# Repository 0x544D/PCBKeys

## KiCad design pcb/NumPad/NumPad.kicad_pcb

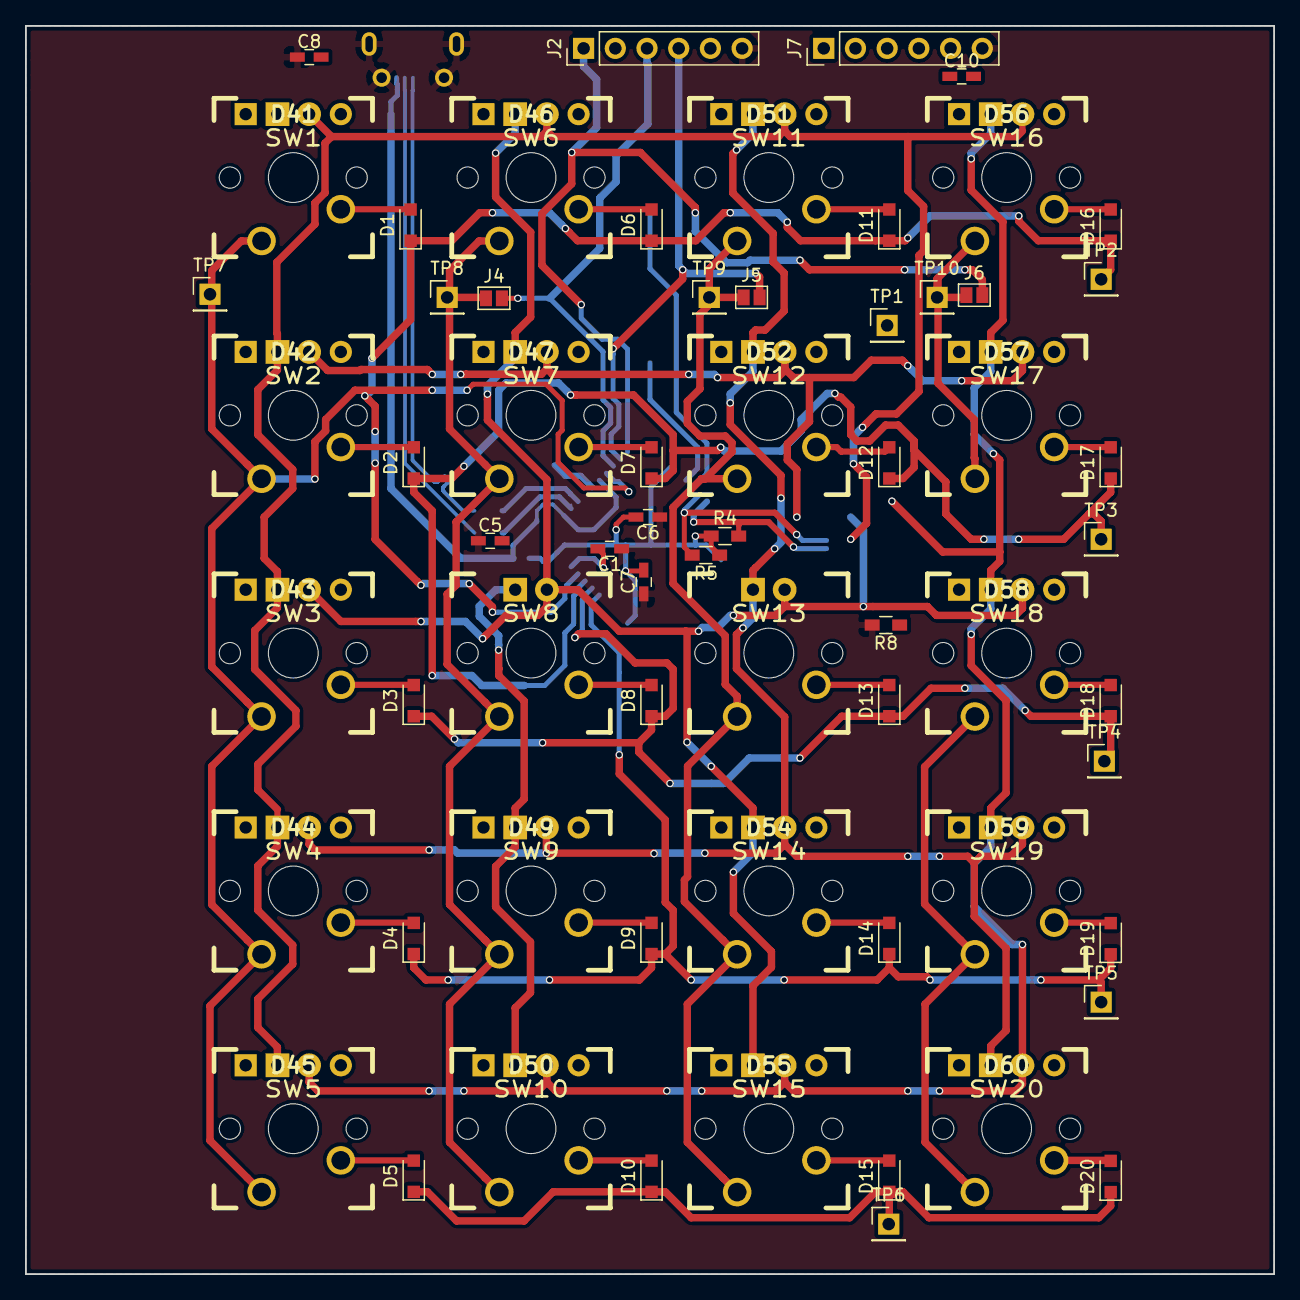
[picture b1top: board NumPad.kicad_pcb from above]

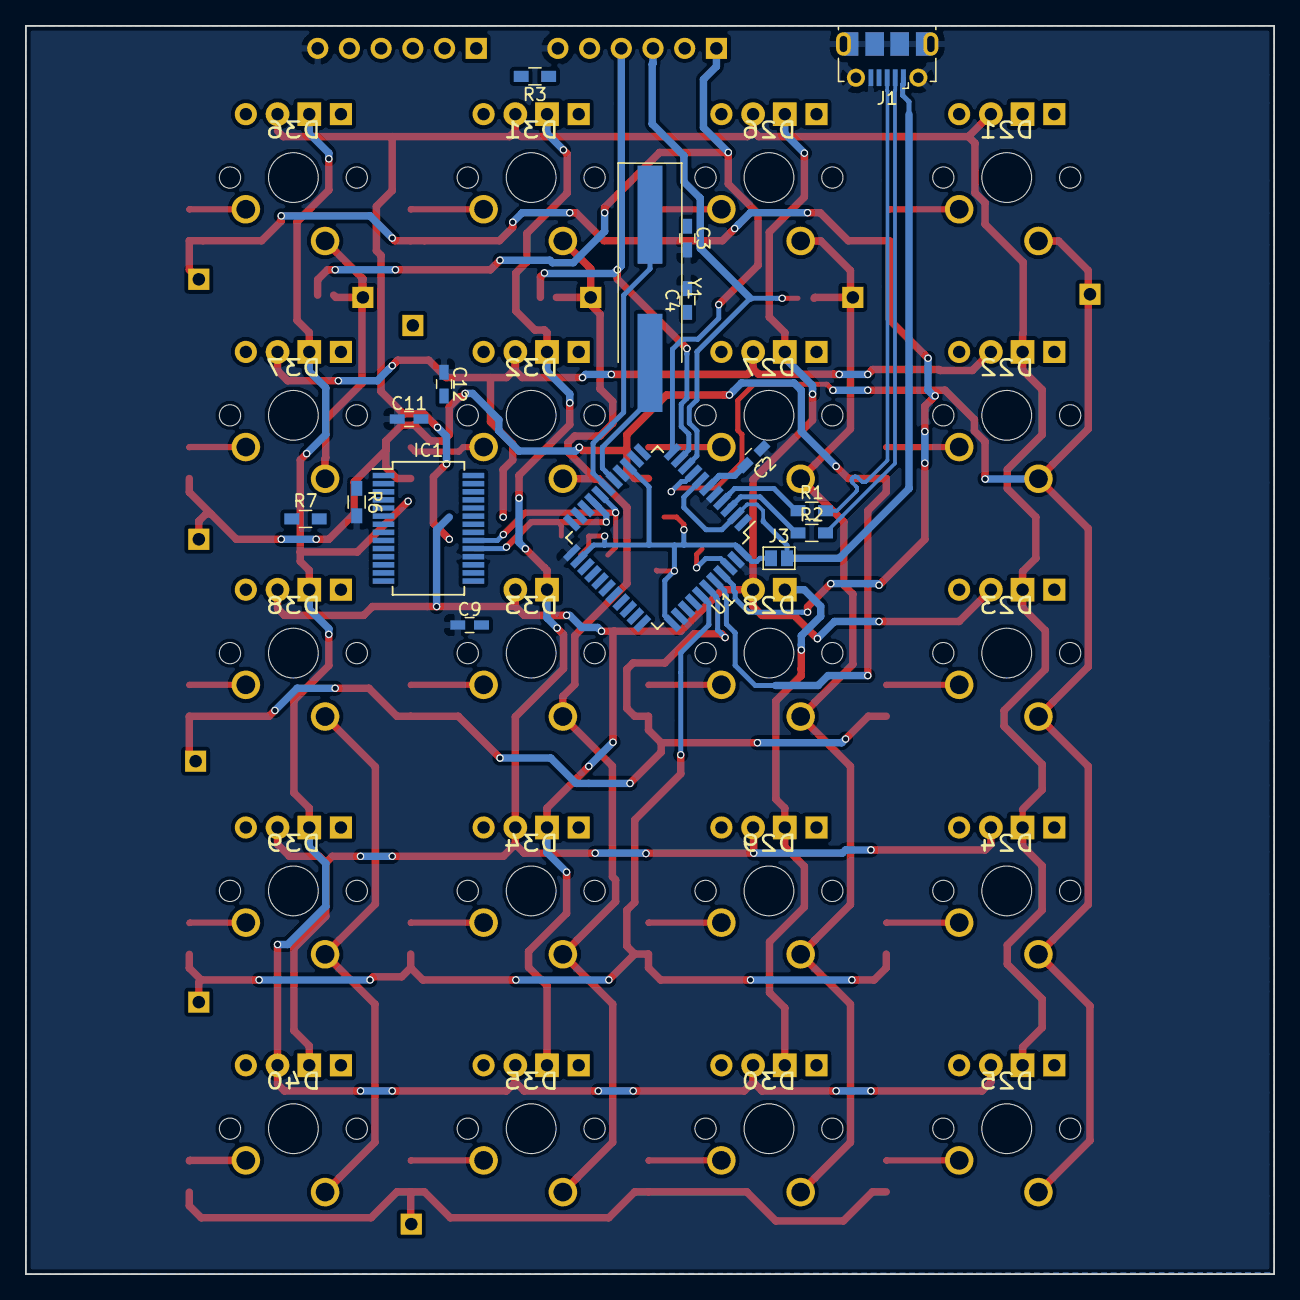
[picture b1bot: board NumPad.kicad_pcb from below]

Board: 2 copper layers, 100.0 x 100.0 mm, 118 parts (16 on the bottom side), 57 nets.

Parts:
C1, C5, C6, C9, C11: 100nF; C_0603_HandSoldering
C2: 1uF; C_0603_HandSoldering
C3, C4: 22pF; C_0603_HandSoldering
C7, C8, C12: 10uF; C_0603_HandSoldering
C10: 220nF; C_0603_HandSoldering
D1: D00; D_SOD-323_HandSoldering
D2: D10; D_SOD-323_HandSoldering
D3: D20; D_SOD-323_HandSoldering
D4: D30; D_SOD-323_HandSoldering
D5: D40; D_SOD-323_HandSoldering
D6: D01; D_SOD-323_HandSoldering
D7: D11; D_SOD-323_HandSoldering
D8: D21; D_SOD-323_HandSoldering
D9: D31; D_SOD-323_HandSoldering
D10: D41; D_SOD-323_HandSoldering
D11: D02; D_SOD-323_HandSoldering
D12: D12; D_SOD-323_HandSoldering
D13: D22; D_SOD-323_HandSoldering
D14: D32; D_SOD-323_HandSoldering
D15: D42; D_SOD-323_HandSoldering
D16: D03; D_SOD-323_HandSoldering
D17: D13; D_SOD-323_HandSoldering
D18: D23; D_SOD-323_HandSoldering
D19: D33; D_SOD-323_HandSoldering
D20: D43; D_SOD-323_HandSoldering
D21: L_+; CHERRY_MX_LED
D22: L_7; CHERRY_MX_LED
D23: L_4; CHERRY_MX_LED
D24: L_1; CHERRY_MX_LED
D25: L_0; CHERRY_MX_LED
D26: L_-; CHERRY_MX_LED
D27: L_8; CHERRY_MX_LED
D28: L_5; CHERRY_MX_LED
D29: L_2; CHERRY_MX_LED
D30: L_,; CHERRY_MX_LED
D31: L_*; CHERRY_MX_LED
D32: L_9; CHERRY_MX_LED
D33: L_6; CHERRY_MX_LED
D34: L_3; CHERRY_MX_LED
D35: L_.; CHERRY_MX_LED
D36: L_/; CHERRY_MX_LED
D37: L_FN2; CHERRY_MX_LED
D38: L_FN1; CHERRY_MX_LED
D39: L_=; CHERRY_MX_LED
D40: L_FN0; CHERRY_MX_LED
D41, D42, D43, D44, D45, D46, D47, D49, D50, D51, D52, D54, D55, D56, D57, D58, D59, D60: D; CHERRY_MX_DIODE
IC1: IS31FL3731; SSOP-28_5.3x10.2mm_Pitch0.65mm
J1: USB_OTG; USB_Micro-B_Molex-105017-0001
J2: ISP; Pin_Header_Straight_1x06_Pitch2.54mm
J3, J4, J5, J6: GS2
J7: Conn_01x06; Pin_Header_Straight_1x06_Pitch2.54mm
R1, R2: 22; R_0603_HandSoldering
R3: 10k; R_0603_HandSoldering
R4, R5, R7: 4k7; R_0603_HandSoldering
R6: 100k; R_0603_HandSoldering
R8: 20k; R_0603_HandSoldering
SW1: +; CHERRY_PCB_100H
SW2: 7; CHERRY_PCB_100H
SW3: 4; CHERRY_PCB_100H
SW4: 1; CHERRY_PCB_100H
SW5: 0; CHERRY_PCB_100H
SW6: -; CHERRY_PCB_100H
SW7: 8; CHERRY_PCB_100H
SW8: 5; CHERRY_PCB_100H
SW9: 2; CHERRY_PCB_100H
SW10: ,; CHERRY_PCB_100H
SW11: *; CHERRY_PCB_100H
SW12: 9; CHERRY_PCB_100H
SW13: 6; CHERRY_PCB_100H
SW14: 3; CHERRY_PCB_100H
SW15: .; CHERRY_PCB_100H
SW16: /; CHERRY_PCB_100H
SW17: FN2; CHERRY_PCB_100H
SW18: FN1; CHERRY_PCB_100H
SW19: =; CHERRY_PCB_100H
SW20: FN0; CHERRY_PCB_100H
TP1, TP2, TP3, TP4, TP5, TP6, TP7, TP8, TP9, TP10: TEST; Pin_Header_Straight_1x01_Pitch2.54mm
U1: ATmega32U4; TQFP-44_10x10mm_Pitch0.8mm
Y1: Crystal; Crystal_SMD_HC49-SD_HandSoldering

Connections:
/Controller/AIN: C10.1, J7.5
/Controller/CA1: D21.1, D22.2, D23.2, D24.2, D25.2, D26.1, D31.1, D36.1, IC1.21
/Controller/CA2: D21.2, D22.1, D27.1, D28.2, D29.2, D30.2, D32.1, D37.1, IC1.22
/Controller/CA3: D23.1, D26.2, D27.2, D28.1, D33.1, D34.2, D35.2, D38.1, IC1.23
/Controller/CA4: D24.1, D29.1, D31.2, D32.2, D33.2, D34.1, D39.1, D40.2, IC1.24
/Controller/CA5: D25.1, D30.1, D35.1, D36.2, D37.2, D38.2, D39.2, D40.1, IC1.25
/Controller/COL0: SW1.1, SW2.1, SW3.1, SW4.1, SW5.1, TP7.1, U1.8
/Controller/COL1: J4.1, SW6.1, SW7.1, SW8.1, SW9.1, SW10.1, TP8.1
/Controller/COL2: J5.1, SW11.1, SW12.1, SW13.1, SW14.1, SW15.1, TP9.1
/Controller/COL3: J6.1, SW16.1, SW17.1, SW18.1, SW19.1, SW20.1, TP10.1
/Controller/D+: R1.1, U1.4
/Controller/D-: R2.1, U1.3
/Controller/INTB: IC1.4, J7.4, R7.2, U1.20
/Controller/MISO: J2.1, J6.2, U1.11
/Controller/MOSI: J2.4, J5.2, U1.10
/Controller/RESET: J2.5, R3.1, U1.13
/Controller/ROW0: D1.1, D6.1, D11.1, D16.1, TP2.1, U1.41
/Controller/ROW1: D2.1, D7.1, D12.1, D17.1, TP3.1, U1.40
/Controller/ROW2: D3.1, D8.1, D13.1, D18.1, TP4.1, U1.39
/Controller/ROW3: D4.1, D9.1, D14.1, D19.1, TP5.1, U1.38
/Controller/ROW4: D5.1, D10.1, D15.1, D20.1, TP6.1, U1.37
/Controller/SCK: J2.3, J4.2, U1.9
/Controller/SCL: IC1.20, J7.2, R5.2, U1.18
/Controller/SDA: IC1.19, J7.3, R4.2, U1.19
/Controller/SHUTDOWN: IC1.3, R6.1, TP1.1, U1.21
/Controller/USB_D+: J1.3, R1.2
/Controller/USB_D-: J1.2, R2.2
GND: C1.1, C2.1, C3.2, C4.2, C5.1, C6.1, C7.1, C8.1, C9.1, C11.1, C12.1, IC1.5, IC1.18, J1.5, J1.6, J2.6, J7.6, R6.2, R8.2, U1.5, U1.15, U1.23, U1.35, U1.43
unnamed: C1.2, U1.42
unnamed: C2.2, U1.6
unnamed: C3.1, U1.17, Y1.1
unnamed: C4.1, U1.16, Y1.2
unnamed: C9.2, IC1.16
unnamed: C10.2, IC1.17
unnamed: D1.2, SW1.2
unnamed: D2.2, SW2.2
unnamed: D3.2, SW3.2
unnamed: D4.2, SW4.2
unnamed: D5.2, SW5.2
unnamed: D6.2, SW6.2
unnamed: D7.2, SW7.2
unnamed: D8.2, SW8.2
unnamed: D9.2, SW9.2
unnamed: D10.2, SW10.2
unnamed: D11.2, SW11.2
unnamed: D12.2, SW12.2
unnamed: D13.2, SW13.2
unnamed: D14.2, SW14.2
unnamed: D15.2, SW15.2
unnamed: D16.2, SW16.2
unnamed: D17.2, SW17.2
unnamed: D18.2, SW18.2
unnamed: D19.2, SW19.2
unnamed: D20.2, SW20.2
unnamed: IC1.6, R8.1
UVCC: J1.1, J3.2, U1.2, U1.7
VCC: C5.2, C6.2, C7.2, C8.2, C11.2, C12.2, IC1.2, J2.2, J3.1, J7.1, R3.2, R4.1, R5.1, R7.1, U1.14, U1.24, U1.34, U1.44

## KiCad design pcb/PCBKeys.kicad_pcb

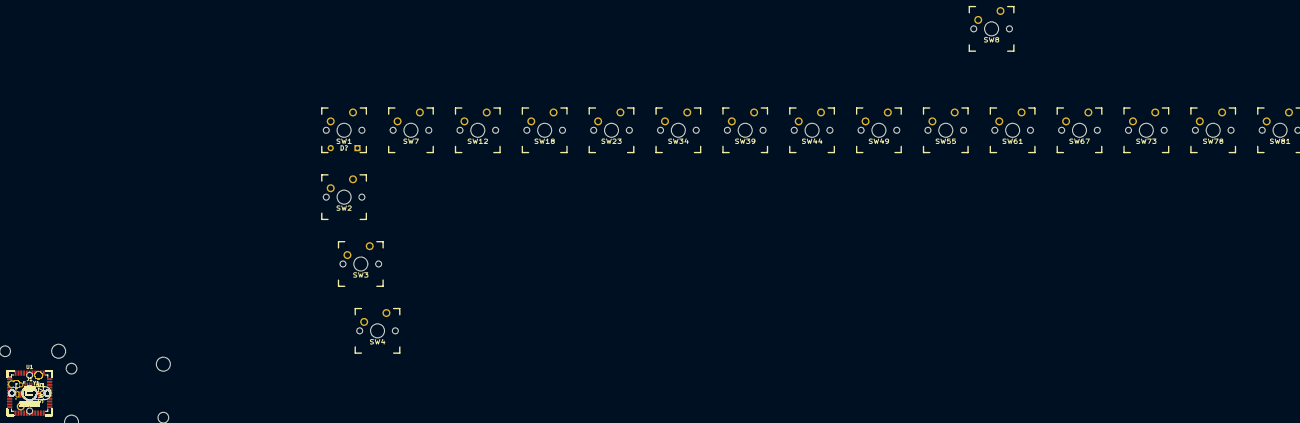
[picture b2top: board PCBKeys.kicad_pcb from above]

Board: 2 copper layers, 187 parts (0 on the bottom side), 119 nets, no tracks yet.

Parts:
C1, C5, C6: 100nF; C_0603_HandSoldering
C2: 1uF; C_0603_HandSoldering
C3, C4: 22pF; C_0603_HandSoldering
C7, C8: 10uF; C_0603_HandSoldering
D1: D00; D_SOD-523
D2: D10; D_SOD-523
D3: D20; D_SOD-523
D4: D30; D_SOD-523
D5: D40; D_SOD-523
D6: D50; D_SOD-523
D7: D01; D_SOD-523
D8: D11; D_SOD-523
D9: D21; D_SOD-523
D10: D41; D_SOD-523
D11: D51; D_SOD-523
D12: D02; D_SOD-523
D13: D12; D_SOD-523
D14: D22; D_SOD-523
D15: D32; D_SOD-523
D16: D42; D_SOD-523
D17: D52; D_SOD-523
D18: D03; D_SOD-523
D19: D13; D_SOD-523
D20: D23; D_SOD-523
D21: D33; D_SOD-523
D22: D43; D_SOD-523
D23: D04; D_SOD-523
D24: D14; D_SOD-523
D25: D24; D_SOD-523
D26: D34; D_SOD-523
D27: D44; D_SOD-523
D28: D05; D_SOD-523
D29: D15; D_SOD-523
D30: D25; D_SOD-523
D31: D35; D_SOD-523
D32: D45; D_SOD-523
D33: D55; D_SOD-523
D34: D06; D_SOD-523
D35: D16; D_SOD-523
D36: D26; D_SOD-523
D37: D36; D_SOD-523
D38: D46; D_SOD-523
D39: D07; D_SOD-523
D40: D17; D_SOD-523
D41: D27; D_SOD-523
D42: D37; D_SOD-523
D43: D47; D_SOD-523
D44: D08; D_SOD-523
D45: D18; D_SOD-523
D46: D28; D_SOD-523
D47: D38; D_SOD-523
D48: D48; D_SOD-523
D49: D09; D_SOD-523
D50: D19; D_SOD-523
D51: D29; D_SOD-523
D52: D39; D_SOD-523
D53: D49; D_SOD-523
D54: D59; D_SOD-523
D55: D0A; D_SOD-523
D56: D1A; D_SOD-523
D57: D2A; D_SOD-523
D58: D3A; D_SOD-523
D59: D4A; D_SOD-523
D60: D5A; D_SOD-523
D61: D0B; D_SOD-523
D62: D1B; D_SOD-523
D63: D2B; D_SOD-523
D64: D3B; D_SOD-523
D65: D4B; D_SOD-523
D66: D5B; D_SOD-523
D67: D0C; D_SOD-523
D68: D1C; D_SOD-523
D69: D2C; D_SOD-523
D70: D3C; D_SOD-523
D71: D4C; D_SOD-523
D72: D5C; D_SOD-523
D73: D0D; D_SOD-523
D74: D1D; D_SOD-523
D75: D2D; D_SOD-523
D76: D3D; D_SOD-523
D77: D5D; D_SOD-523
D78: D0E; D_SOD-523
D79: D4E; D_SOD-523
D80: D5E; D_SOD-523
D81: D0F; D_SOD-523
D82: D1F; D_SOD-523
D83: D2F; D_SOD-523
D84: D3F; D_SOD-523
D85: D4F; D_SOD-523
D86: D5F; D_SOD-523
D?: DIODE; CHERRY_MX_DIODE
J1: USB_OTG; USB_Micro-B_Molex-105017-0001
R1, R2: 22; CHERRY_PCB_100H
R3: 10k; CHERRY_PCB_100H
SW1: ESC; CHERRY_PCB_100H
SW2: CIRC; CHERRY_PCB_100H
SW3: TAB; CHERRY_PCB_150H
SW4: CAPS; CHERRY_PCB_175H
SW5: SHIFT_L; CHERRY_PCB_125H
SW6: CTRL_L; CHERRY_PCB_100H
SW7: F1; CHERRY_PCB_100H
SW8: 1; CHERRY_PCB_100H
SW9: Q; CHERRY_PCB_100H
SW10: <; CHERRY_PCB_100H
SW11: WIN_L; CHERRY_PCB_100H
SW12: F2; CHERRY_PCB_100H
SW13: 2; CHERRY_PCB_100H
SW14: W; CHERRY_PCB_100H
SW15: A; CHERRY_PCB_100H
SW16: Y; CHERRY_PCB_100H
SW17: ALT; CHERRY_PCB_100H
SW18: F3; CHERRY_PCB_100H
SW19: 3; CHERRY_PCB_100H
SW20: E; CHERRY_PCB_100H
SW21: S; CHERRY_PCB_100H
SW22: X; CHERRY_PCB_100H
SW23: F4; CHERRY_PCB_100H
SW24: 4; CHERRY_PCB_100H
SW25: R; CHERRY_PCB_100H
SW26: D; CHERRY_PCB_100H
SW27: C; CHERRY_PCB_100H
SW28: F5; CHERRY_PCB_100H
SW29: 5; CHERRY_PCB_100H
SW30: T; CHERRY_PCB_100H
SW31: F; CHERRY_PCB_100H
SW32: V; CHERRY_PCB_100H
SW33: SPACE; CHERRY_PCB_600H
SW34: F6; CHERRY_PCB_100H
SW35: 6; CHERRY_PCB_100H
SW36: Z; CHERRY_PCB_100H
SW37: G; CHERRY_PCB_100H
SW38: B; CHERRY_PCB_100H
SW39: F7; CHERRY_PCB_100H
SW40: 7; CHERRY_PCB_100H
SW41: U; CHERRY_PCB_100H
SW42: H; CHERRY_PCB_100H
SW43: N; CHERRY_PCB_100H
SW44: F8; CHERRY_PCB_100H
SW45: 8; CHERRY_PCB_100H
SW46: I; CHERRY_PCB_100H
SW47: J; CHERRY_PCB_100H
SW48: M; CHERRY_PCB_100H
SW49: F9; CHERRY_PCB_100H
SW50: 9; CHERRY_PCB_100H
SW51: O; CHERRY_PCB_100H
SW52: K; CHERRY_PCB_100H
SW53: ,; CHERRY_PCB_100H
SW54: ALTGR; CHERRY_PCB_100H
SW55: F10; CHERRY_PCB_100H
SW56: 0; CHERRY_PCB_100H
SW57: P; CHERRY_PCB_100H
SW58: L; CHERRY_PCB_100H
SW59: .; CHERRY_PCB_100H
SW60: WIN_R; CHERRY_PCB_100H
SW61: F11; CHERRY_PCB_100H
SW62: ?; CHERRY_PCB_100H
SW63: Ü; CHERRY_PCB_100H
SW64: Ö; CHERRY_PCB_100H
SW65: -; CHERRY_PCB_100H
SW66: FN0; CHERRY_PCB_100H
SW67: F12; CHERRY_PCB_100H
SW68: ACC; CHERRY_PCB_100H
SW69: *; CHERRY_PCB_100H
SW70: Ä; CHERRY_PCB_100H
SW71: SHIFT_R; CHERRY_PCB_175H
SW72: CTRL_R; CHERRY_PCB_100H
SW73: POS1; CHERRY_PCB_100H
SW74: BSPC; CHERRY_PCB_200H
SW75: ENTER; CHERRY_PCB_ISOR
SW76: #; CHERRY_PCB_100H
SW77: LEFT; CHERRY_PCB_100H
SW78: EINFG; CHERRY_PCB_100H
SW79: UP; CHERRY_PCB_100H
SW80: DOWN; CHERRY_PCB_100H
SW81: ENDE; CHERRY_PCB_100H
SW82: ENTF; CHERRY_PCB_100H
SW83: BILD_U; CHERRY_PCB_100H
SW84: BILD_D; CHERRY_PCB_100H
SW85: FN1; CHERRY_PCB_100H
SW86: RIGHT; CHERRY_PCB_100H
U1: ATmega32U4; TQFP-44_10x10mm_Pitch0.8mm
Y1: Crystal; Crystal_HC52-6mm_Vertical

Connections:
/Controller/COL0: SW1.1, SW2.1, SW3.1, SW4.1, SW5.1, SW6.1, U1.28
/Controller/COL1: SW7.1, SW8.1, SW9.1, SW10.1, SW11.1, U1.29
/Controller/COL2: SW12.1, SW13.1, SW14.1, SW15.1, SW16.1, SW17.1, U1.30
/Controller/COL3: SW18.1, SW19.1, SW20.1, SW21.1, SW22.1, U1.12
/Controller/COL4: SW23.1, SW24.1, SW25.1, SW26.1, SW27.1, U1.31
/Controller/COL5: SW28.1, SW29.1, SW30.1, SW31.1, SW32.1, SW33.1, U1.32
/Controller/COL6: SW34.1, SW35.1, SW36.1, SW37.1, SW38.1, U1.18
/Controller/COL7: SW39.1, SW40.1, SW41.1, SW42.1, SW43.1, U1.19
/Controller/COL8: SW44.1, SW45.1, SW46.1, SW47.1, SW48.1, U1.20
/Controller/COL9: SW49.1, SW50.1, SW51.1, SW52.1, SW53.1, SW54.1, U1.21
/Controller/COL10: SW55.1, SW56.1, SW57.1, SW58.1, SW59.1, SW60.1, U1.25
/Controller/COL11: SW61.1, SW62.1, SW63.1, SW64.1, SW65.1, SW66.1, U1.22
/Controller/COL12: SW67.1, SW68.1, SW69.1, SW70.1, SW71.1, SW72.1, U1.26
/Controller/COL13: SW73.1, SW74.1, SW75.1, SW76.1, SW77.1, U1.27
/Controller/COL14: SW78.1, SW79.1, SW80.1, SW81.1, SW82.1, SW83.1, SW84.1, SW85.1, SW86.1, U1.33
/Controller/D+: R1.1, U1.4
/Controller/D-: R2.1, U1.3
/Controller/ROW0: D1.1, D7.1, D12.1, D18.1, D23.1, D28.1, D34.1, D39.1, D44.1, D49.1, D55.1, D61.1, D67.1, D73.1, D78.1, D81.1, U1.41
/Controller/ROW1: D2.1, D8.1, D13.1, D19.1, D24.1, D29.1, D35.1, D40.1, D45.1, D50.1, D56.1, D62.1, D68.1, D74.1, D82.1, U1.40
/Controller/ROW2: D3.1, D9.1, D14.1, D20.1, D25.1, D30.1, D36.1, D41.1, D46.1, D51.1, D57.1, D63.1, D69.1, D75.1, D83.1, U1.39
/Controller/ROW3: D4.1, D15.1, D21.1, D26.1, D31.1, D37.1, D42.1, D47.1, D52.1, D58.1, D64.1, D70.1, D76.1, D84.1, U1.38
/Controller/ROW4: D5.1, D10.1, D16.1, D22.1, D27.1, D32.1, D38.1, D43.1, D48.1, D53.1, D59.1, D65.1, D71.1, D79.1, D85.1, U1.37
/Controller/ROW5: D6.1, D11.1, D17.1, D33.1, D54.1, D60.1, D66.1, D72.1, D77.1, D80.1, D86.1, U1.36
GND: C1.1, C2.1, C3.2, C4.2, C5.1, C6.1, C7.1, C8.1, J1.5, J1.6, U1.5, U1.15, U1.23, U1.35, U1.43
unnamed: C1.2, U1.42
unnamed: C2.2, U1.6
unnamed: C3.1, U1.17, Y1.1
unnamed: C4.1, U1.16, Y1.2
unnamed: D1.2, SW1.2
unnamed: D2.2, SW2.2
unnamed: D3.2, SW3.2
unnamed: D4.2, SW4.2
unnamed: D5.2, SW5.2
unnamed: D6.2, SW6.2
unnamed: D7.2, SW7.2
unnamed: D8.2, SW8.2
unnamed: D9.2, SW9.2
unnamed: D10.2, SW10.2
unnamed: D11.2, SW11.2
unnamed: D12.2, SW12.2
unnamed: D13.2, SW13.2
unnamed: D14.2, SW14.2
unnamed: D15.2, SW15.2
unnamed: D16.2, SW16.2
unnamed: D17.2, SW17.2
unnamed: D18.2, SW18.2
unnamed: D19.2, SW19.2
unnamed: D20.2, SW20.2
unnamed: D21.2, SW21.2
unnamed: D22.2, SW22.2
unnamed: D23.2, SW23.2
unnamed: D24.2, SW24.2
unnamed: D25.2, SW25.2
unnamed: D26.2, SW26.2
unnamed: D27.2, SW27.2
unnamed: D28.2, SW28.2
unnamed: D29.2, SW29.2
unnamed: D30.2, SW30.2
unnamed: D31.2, SW31.2
unnamed: D32.2, SW32.2
unnamed: D33.2, SW33.2
unnamed: D34.2, SW34.2
unnamed: D35.2, SW35.2
unnamed: D36.2, SW36.2
unnamed: D37.2, SW37.2
unnamed: D38.2, SW38.2
unnamed: D39.2, SW39.2
unnamed: D40.2, SW40.2
unnamed: D41.2, SW41.2
unnamed: D42.2, SW42.2
unnamed: D43.2, SW43.2
unnamed: D44.2, SW44.2
unnamed: D45.2, SW45.2
unnamed: D46.2, SW46.2
unnamed: D47.2, SW47.2
unnamed: D48.2, SW48.2
unnamed: D49.2, SW49.2
unnamed: D50.2, SW50.2
unnamed: D51.2, SW51.2
unnamed: D52.2, SW52.2
unnamed: D53.2, SW53.2
unnamed: D54.2, SW54.2
unnamed: D55.2, SW55.2
unnamed: D56.2, SW56.2
unnamed: D57.2, SW57.2
unnamed: D58.2, SW58.2
unnamed: D59.2, SW59.2
unnamed: D60.2, SW60.2
unnamed: D61.2, SW61.2
unnamed: D62.2, SW62.2
unnamed: D63.2, SW63.2
unnamed: D64.2, SW64.2
unnamed: D65.2, SW65.2
unnamed: D66.2, SW66.2
unnamed: D67.2, SW67.2
unnamed: D68.2, SW68.2
unnamed: D69.2, SW69.2
unnamed: D70.2, SW70.2
unnamed: D71.2, SW71.2
unnamed: D72.2, SW72.2
unnamed: D73.2, SW73.2
unnamed: D74.2, SW74.2
unnamed: D75.2, SW75.2
unnamed: D76.2, SW76.2
unnamed: D77.2, SW77.2
unnamed: D78.2, SW78.2
unnamed: D79.2, SW79.2
unnamed: D80.2, SW80.2
unnamed: D81.2, SW81.2
unnamed: D82.2, SW82.2
unnamed: D83.2, SW83.2
unnamed: D84.2, SW84.2
unnamed: D85.2, SW85.2
unnamed: D86.2, SW86.2
unnamed: J1.2, R2.2
unnamed: J1.3, R1.2
unnamed: R3.1, U1.13
UVCC: J1.1, U1.2, U1.7
VCC: C5.2, C6.2, C7.2, C8.2, R3.2, U1.14, U1.24, U1.34, U1.44

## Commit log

2018-03-25 added pcb files
2018-03-25 changes in schematic
2018-03-27 almost finished NumPad schematic
2018-03-28 started Numpad Layout
2018-04-07 changes in Numpad
2018-04-07 changes in NumPad layout
2018-04-08 NumPad row and col routed
